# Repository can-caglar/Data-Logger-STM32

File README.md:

# Serial Snooper

The Serial Snooper is a UART data logger with automatic baud rate detection, real-time data stamping and a command-line-interface for configuration, running on an STM32F3 microcontroller.

It is utilised in an R&D setting to easily capture logs from devices to speed up catching software and hardware bugs.

<i> This project started out as a submission for the final project in the course "Making Embedded Systems" by Elecia White, and evolved into a complete functional product used professionally. The report for the project submitted to the course can be found [here](https://docs.google.com/document/d/1QN5CVr99LwbAlFGOjgETou2btL8RMqJVu_yTGeXLMHs/edit?usp=sharing). </i>

## The Final Product

<center>
<image src="resource\hw_image_1.jpg">
<i>PCBA Front</i>
<br>
<br>
<image src="resource\hw_image_2.jpg">
<i>PCBA Back</i>
<br>
<br>
</center>

## Description of Operation

1. Plug in USB (5V - resettable fuse limits current to 500mA incase of short circuits damaging the power source).
2. Device powers up, indicated by the green LED.
3. A short moment later, the red LED lights up, indicating that the SD card was successfully initialised.
4. Plug in DB9 cable for the device you wish to snoop. The baud rate will be automatically detected.
5. The yellow LED will toggle for every character received.
6. The blue LED will toggle for every successful SD card write.
7. When ready, power down the device by removing the USB cable and remove the SD card.

## Schematic

<center>
<image src="HardwareDesign\hardwareImages_v1\schematic_png.PNG">
<i>Partial schematic. At the heart of the device is a STM32F303 microcontroller.</i>
</center>
<br>

The full hardware schematic can be found on [Github](HardwareDesign/hardwareImages_v1/serial_snooper_schematic.pdf).

## Design Block Diagram

<center>

<i>Software Block Diagram</i>
</center>

## Prototype

A prototype board was created to aid development.

Headers have been soldered to a perforated board. A mixture of wire wrapping and soldering used for the connections.

### The working prototype

### Pinouts

# Demo 

All demonstrations below are from the prototype device using the software in this repository.

## Command Line Interface (CLI)

The CLI is used to:

- Ascertain the software version number
- Send commands:
  - Get DIP switch setting.
  - Get the current time.
  - Set the current time.

For example:
<center>

</center>

## Example Data Saved on SD Card

The received data is timestamped and saved to the SD card. The filesystem being used is Fatfs (middleware software for this was provided by STM32 Cube).

In the example below, nearly 30,000 characters were sent over the course of 68 seconds (at 115200 BR) and all data was transferred successfully.

*(The text file below is generated by the Serial Snooper and can be found as resource/example_log.TXT)*

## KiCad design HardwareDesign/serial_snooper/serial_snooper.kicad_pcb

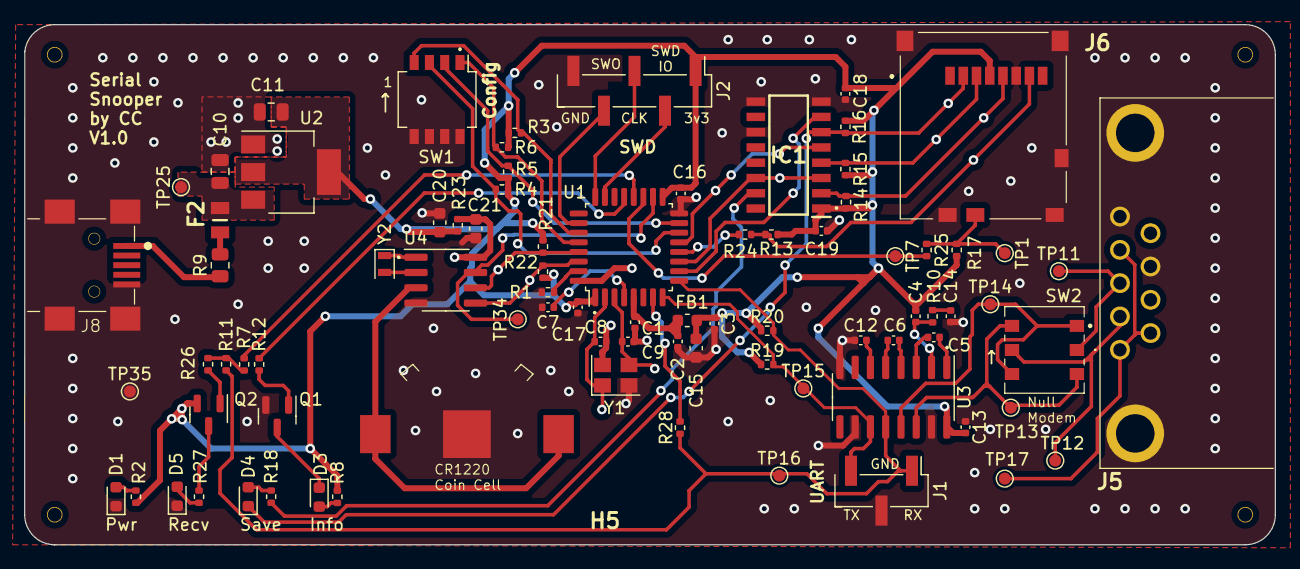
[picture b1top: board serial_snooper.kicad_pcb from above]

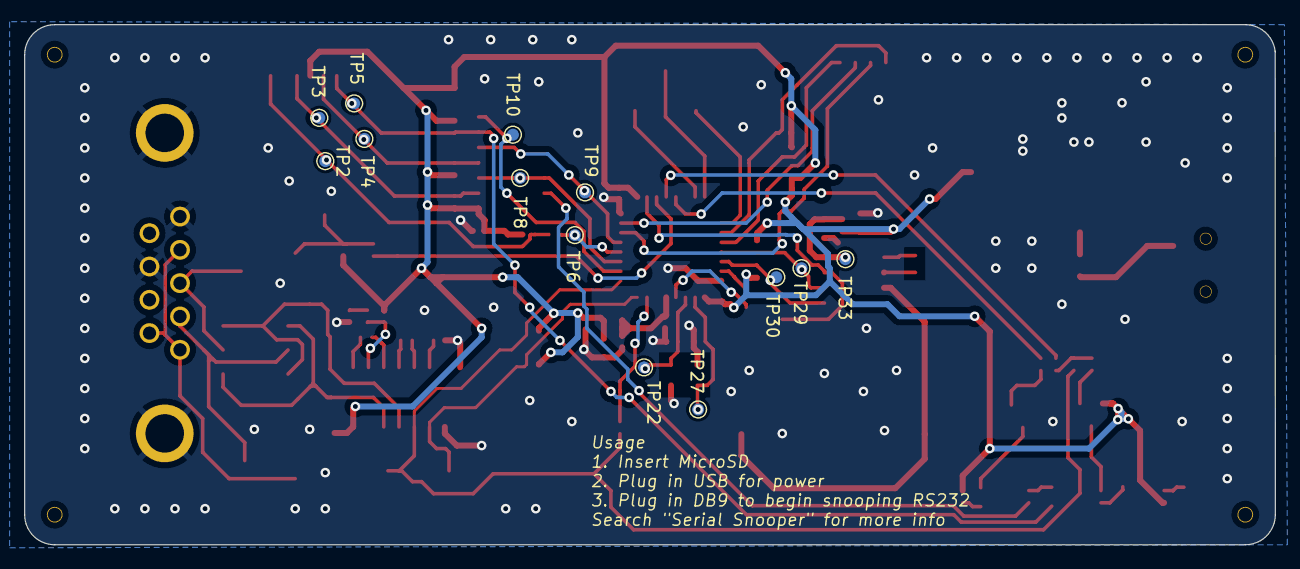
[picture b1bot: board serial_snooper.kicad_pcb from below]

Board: 2 copper layers, 104.0 x 43.2 mm, 101 parts (13 on the bottom side), 61 nets.

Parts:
C1: 10n; C_0402_1005Metric
C2, C3: 1u; C_0402_1005Metric
C4, C5, C6, C7, C12, C13, C14, C16, C17, C18, C19: 100n; C_0402_1005Metric
C8, C9: 15p; C_0402_1005Metric
C10, C11: 22u; C_0805_2012Metric
C15, C20, C21: 10u; C_0603_1608Metric
D1: GREEN; LED_0603_1608Metric
D3: RED; LED_0603_1608Metric
D4: RED_SD; LED_0603_1608Metric
D5: YELLOW; LED_0603_1608Metric
F2: 0ZCK0020FF2G; FUSC2214X100N
FB1: 120R; L_0603_1608Metric
H1, H2, H3, H4: MountingHole; ToolingHole
H5: 2894
IC1: 74HC4050D,653; SOIC127P600X175-16N
J1: Conn_01x03_Pin; PinHeader_1x03_P2.54mm_Vertical_SMD_Pin1Left
J2: Conn_01x05_Pin; PinHeader_1x05_P2.54mm_Vertical_SMD_Pin1Left
J5: L717SDE09P1ACH
J6: Micro_SD_Card_Det1; 5025700893
J8: USB_B_Mini; USB-MINI-10033526-N3212LF
Q1: MMBT3904; SOT-23
Q2: MMBT3906; SOT-23
R1, R3, R4, R5, R6: 10k; R_0402_1005Metric
R2, R12, R18, R23, R26: 1k5; R_0402_1005Metric
R7, R10: DNP; R_0402_1005Metric
R8, R27: 330R; R_0402_1005Metric
R9: 0R; R_0805_2012Metric
R11, R24, R25, R28: 0R; R_0402_1005Metric
R13, R14, R15, R16, R17, R19, R20: 47k; R_0402_1005Metric
R21, R22: 10K; R_0402_1005Metric
SW1: SW_DIP_x04; SW_DIP_SPSTx04_Slide_Omron_A6H-4101_W6.15mm_P1.27mm
SW2: SW_DPDT_x2; DPDT-SMD-MS-22D28G2-B
TP1, TP2, TP3, TP4, TP5, TP6, TP7, TP8, TP9, TP10, TP11, TP12, TP13, TP14, TP15, TP16, TP17, TP22, TP25, TP27, TP29, TP30, TP33, TP34, TP35: TestPoint; TestPoint_Pad_D1.0mm
U1: STM32F303K8T6; LQFP-32_7x7mm_P0.8mm
U2: AMS1117-3.3; SOT-223-3_TabPin2
U3: MAX3232; SOIC-16_3.9x9.9mm_P1.27mm
U4: PCF8523T; SOIC-8_3.9x4.9mm_P1.27mm
Y1: 16MHz; Crystal_SMD_3225-4Pin_3.2x2.5mm
Y2: 32.768; Crystal_SMD_2012-2Pin_2.0x1.2mm

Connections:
+3.3V: C3.1, C4.2, C11.1, C13.2, C15.1, C16.1, C17.1, C18.1, C19.1, C20.1, FB1.1, IC1.1 (VCC), J2.1, J6.4 (VDD), Q2.2 (E), R2.1, R3.1, R4.1, R5.1, R6.1, R8.2, R13.1, R14.1, R15.1, R16.1, R17.1, R19.1, R20.1, R21.1, R22.1, R23.2, U1.1 (VDD), U1.17 (VDD), U2.2 (VO), U3.16 (VCC)
+3.3VA: C1.1, C2.1, FB1.2, U1.5 (VDDA)
/BOOT0: R1.2, U1.31 (BOOT0)
/CARD_DETECT: R25.1, TP7.1, U1.19 (PA9)
/COMMS_LED: R7.1, U1.20 (PA10)
/DIPSWITCH_1: R6.2, SW1.1, U1.28 (PB5)
/DIPSWITCH_2: R5.2, SW1.2, U1.15 (PB1)
/DIPSWITCH_3: R4.2, SW1.3, U1.14 (PB0)
/DIPSWITCH_4: R3.2, SW1.4, U1.27 (PB4)
/HSE_IN: C8.1, TP27.1, U1.2 (PF0), Y1.1
/HSE_OUT: C9.1, TP22.1, U1.3 (PF1), Y1.3
/I2C1_SCL: R21.2, TP29.1, U1.29 (PB6), U4.6 (SCL)
/I2C1_SDA: R22.2, TP30.1, U1.30 (PB7), U4.5 (SDA)
/NRST: C7.1, U1.4 (NRST)
/PWR_LED_C: D1.2 (A), R2.2
/RS232-UART/C1+: C5.1, U3.1 (C1+)
/RS232-UART/C1-: C5.2, U3.3 (C1-)
/RS232-UART/C2+: C6.1, U3.4 (C2+)
/RS232-UART/C2-: C6.2, U3.5 (C2-)
/RS232-UART/DB9_RXD: J5.2, SW2.5 (B), TP12.1
/RS232-UART/DB9_TXD: J5.3, SW2.2 (B), TP11.1
/RS232-UART/R1IN: SW2.1 (A), SW2.6 (C), TP14.1, U3.13 (R1IN)
/RS232-UART/T1OUT: SW2.3 (C), SW2.4 (A), TP13.1, U3.14 (T1OUT)
/RS232-UART/VS+: C4.1, R10.1, U3.2 (VS+)
/RS232-UART/VS-: C12.2, U3.6 (VS-)
/RTC_IRQ: TP34.1, U1.18 (PA8), U4.7 (~INT1/CLKOUT)
/RealtimeClock/Battery+: H5.1 (+), H5.2 (-), U4.3 (VBAT)
/RealtimeClock/RTC_Vdd: C21.1, R23.1, TP33.1, U4.8 (VDD)
/SD-card-adapter/SD_CLK: IC1.2 (1Y), J6.5 (CLK), R14.2, TP3.1
/SD-card-adapter/SD_CS: D4.1 (K), IC1.6 (3Y), J6.2 (DAT3/CD), R16.2, TP5.1
/SD-card-adapter/SD_DETECT: J6.9 (DET), R17.2, R25.2, TP1.1
/SD-card-adapter/SD_DI: IC1.4 (2Y), J6.3 (CMD), R15.2, TP4.1
/SD-card-adapter/SD_DO: J6.7 (DAT0), R13.2, R24.2, TP2.1
/SD-card-adapter/SD_LED_ANODE: D4.2 (A), R18.2
/SPI1_CLK: IC1.3 (1A), IC1.14 (6A), TP8.1, U1.11 (PA5)
/SPI1_CS: IC1.7 (3A), TP10.1, U1.10 (PA4)
/SPI1_MISO: R24.1, TP6.1, U1.12 (PA6)
/SPI1_MOSI: IC1.5 (2A), TP9.1, U1.13 (PA7)
/STATUS_LED: R12.2, U1.21 (PA11)
/SWCLK: J2.3, U1.24 (PA14)
/SWDIO: J2.2, U1.23 (PA13)
/TIM2_CH2: R28.2, U1.7 (PA1)
/TRACE_SWO: J2.4, U1.26 (PB3)
/USART2_RX: J1.1, R11.1, R20.2, R28.1, TP16.1, U1.9 (PA3), U3.12 (R1OUT)
/USART2_TX: J1.3, R19.2, TP15.1, U1.8 (PA2), U3.11 (T1IN)
/VBUS_after_fuse: C10.1, F2.2, TP25.1, U2.3 (VI)
GND: C1.2, C2.2, C3.2, C7.2, C8.2, C9.2, C10.2, C11.2, C12.1, C13.1, C14.2, C15.2, C16.2, C17.2, C18.2, C19.2, C20.2, C21.2, D1.1 (K), D5.1 (K), H5.MP1, IC1.8 (GND), IC1.9 (4A), IC1.11 (5A), J1.2, J2.5, J5.5, J5.8, J5.MH1, J5.MH2, J6.6 (VSS), J6.10 (SHIELD), J8.5 (GND), J8.6 (Shield), Q1.2 (E), R1.1, SW1.5, SW1.6, SW1.7, SW1.8, TP35.1, U1.16 (VSS), U1.32 (VSS), U2.1 (GND), U3.8 (R2IN), U3.10 (T2IN), U3.15 (GND), U4.4 (VSS), Y1.2, Y1.4
unnamed: C14.1, R10.2
unnamed: D3.2 (A), R8.1
unnamed: D3.1 (K), Q1.3 (C)
unnamed: D5.2 (A), R27.1
unnamed: F2.1, R9.2
unnamed: IC1.15 (6Y), R18.1
unnamed: J5.1, J5.4, J5.6, TP17.1
unnamed: J8.1 (VBUS), R9.1
unnamed: Q1.1 (B), R12.1
unnamed: Q2.1 (B), R26.1
unnamed: Q2.3 (C), R27.2
unnamed: R7.2, R11.2, R26.2
unnamed: U4.1 (OSCI), Y2.1
unnamed: U4.2 (OSCO), Y2.2

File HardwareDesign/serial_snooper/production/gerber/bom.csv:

Designator,Footprint,Quantity,Value,LCSC Part #
C1,0402,1,10n,
"C10, C11",0805,2,22u,
"C12, C13, C14, C16, C17, C18, C19, C4, C5, C6, C7",0402,11,100n,
"C15, C20, C21",0603,3,10u,
"C2, C3",0402,2,1u,
"C8, C9",0402,2,15p,
D1,0603,1,GREEN,
D3,0603,1,RED,
D4,0603,1,RED_SD,
D5,0603,1,YELLOW,
F2,FUSC2214X100N,1,0ZCK0020FF2G,
FB1,0603,1,120R,
"H1, H2, H3, H4",ToolingHole,4,MountingHole,
H5,2894,1,2894,
IC1,SOIC127P600X175-16N,1,"74HC4050D,653",C43181
J1,PinHeader_1x03_P2.54mm_Vertical_SMD_Pin1Left,1,Conn_01x03_Pin,C5160786
J2,PinHeader_1x05_P2.54mm_Vertical_SMD_Pin1Left,1,Conn_01x05_Pin,
J5,L717SDE09P1ACH,1,L717SDE09P1ACH,
J6,5025700893,1,Micro_SD_Card_Det1,C429846
J8,USB-MINI-10033526-N3212LF,1,USB_B_Mini,C428494
Q1,SOT-23,1,MMBT3904,
Q2,SOT-23,1,MMBT3906,
"R1, R21, R22, R3, R4, R5, R6",0402,7,10k,
"R10, R7",0402,2,DNP,
"R11, R24, R25, R28",0402,4,0R,
"R12, R18, R2, R23, R26",0402,5,1k5,
"R13, R14, R15, R16, R17, R19, R20",0402,7,47k,
"R27, R8",0402,2,330R,
R9,0805,1,0R,
SW1,SW_DIP_SPSTx04_Slide_Omron_A6H-4101_W6.15mm_P1.27mm,1,SW_DIP_x04,
SW2,DPDT-SMD-MS-22D28G2-B,1,SW_DPDT_x2,C2939266
"TP1, TP10, TP11, TP12, TP13, TP14, TP15, TP16, TP17, TP2, TP22, TP25, TP27, TP29, TP3, TP30, TP33, TP34, TP35, TP4, TP5, TP6, TP7, TP8, TP9",TestPoint_Pad_D1.0mm,25,TestPoint,
U1,LQFP-32_7x7mm_P0.8mm,1,STM32F303K8T6,C118318
U2,SOT-223-3_TabPin2,1,AMS1117-3.3,C351784
U3,SOIC-16_3.9x9.9mm_P1.27mm,1,MAX3232,C193666
U4,SOIC-8_3.9x4.9mm_P1.27mm,1,PCF8523T,C2651516
Y1,Crystal_SMD_3225-4Pin_3.2x2.5mm,1,16MHz,C279610
Y2,Crystal_SMD_2012-2Pin_2.0x1.2mm,1,32.768,C252397

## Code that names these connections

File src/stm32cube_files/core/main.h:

/* USER CODE BEGIN Header */
/**
  ******************************************************************************
  * @file           : main.h
  * @brief          : Header for main.c file.
  *                   This file contains the common defines of the application.
  ******************************************************************************
  * @attention
  *
  * Copyright (c) 2022 STMicroelectronics.
  * All rights reserved.
  *
  * This software is licensed under terms that can be found in the LICENSE file
  * in the root directory of this software component.
  * If no LICENSE file comes with this software, it is provided AS-IS.
  *
  ******************************************************************************
  */
/* USER CODE END Header */

/* Define to prevent recursive inclusion -------------------------------------*/
#ifndef __MAIN_H
#define __MAIN_H

#ifdef __cplusplus
extern "C" {
#endif

/* Includes ------------------------------------------------------------------*/
#include "stm32f3xx_hal.h"

/* Private includes ----------------------------------------------------------*/
/* USER CODE BEGIN Includes */

/* USER CODE END Includes */

/* Exported types ------------------------------------------------------------*/
/* USER CODE BEGIN ET */

/* USER CODE END ET */

/* Exported constants --------------------------------------------------------*/
/* USER CODE BEGIN EC */

/* USER CODE END EC */

/* Exported macro ------------------------------------------------------------*/
/* USER CODE BEGIN EM */

/* USER CODE END EM */

/* Exported functions prototypes ---------------------------------------------*/
void Error_Handler(void);

/* USER CODE BEGIN EFP */
#define CMX_FATFS       (1U << 0)
#define CMX_UART        (1U << 1) // with interrupt
#define CMX_I2C         (1U << 2)
#define CMX_UART_POLL   (1U << 3)

void SystemClock_Config(void);
void CubeMX_SystemInit(unsigned int sys);

/* USER CODE END EFP */

/* Private defines -----------------------------------------------------------*/
// TODO remove the unused peripheral defines
#define CS_I2C_SPI_Pin GPIO_PIN_3
#define CS_I2C_SPI_GPIO_Port GPIOE
#define PC14_OSC32_IN_Pin GPIO_PIN_14
#define PC14_OSC32_IN_GPIO_Port GPIOC
#define PC15_OSC32_OUT_Pin GPIO_PIN_15
#define PC15_OSC32_OUT_GPIO_Port GPIOC
#define PH0_OSC_IN_Pin GPIO_PIN_0
#define PH0_OSC_IN_GPIO_Port GPIOH
#define PH1_OSC_OUT_Pin GPIO_PIN_1
#define PH1_OSC_OUT_GPIO_Port GPIOH
#define OTG_FS_PowerSwitchOn_Pin GPIO_PIN_0
#define OTG_FS_PowerSwitchOn_GPIO_Port GPIOC
#define PDM_OUT_Pin GPIO_PIN_3
#define PDM_OUT_GPIO_Port GPIOC
#define B1_Pin GPIO_PIN_0
#define B1_GPIO_Port GPIOA
#define I2S3_WS_Pin GPIO_PIN_4
#define I2S3_WS_GPIO_Port GPIOA

#define SPI1_SCK_Pin GPIO_PIN_5
#define SPI1_SCK_GPIO_Port GPIOA
#define SPI1_MISO_Pin GPIO_PIN_6
#define SPI1_MISO_GPIO_Port GPIOA
#define SPI1_MOSI_Pin GPIO_PIN_7
#define SPI1_MOSI_GPIO_Port GPIOA

/* USER CODE BEGIN Private defines */
#define SD_CS_Pin GPIO_PIN_4
#define SD_CS_GPIO_Port GPIOA
#define SD_SPI_HANDLE hspi1
/* USER CODE END Private defines */

#ifdef __cplusplus
}
#endif

#endif /* __MAIN_H */

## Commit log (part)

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2022-07-02 feat: function isConfiguredAsOutput - not tested yet
2022-07-02 feat: isConfiguredAsOutput passes tests but needs refactoring
2022-07-13 compiles on target. making it actually work on target too.
    Started to enable peripheral clocks.
    Aded a new GPIOA define such that our RAM version and register version will work
    seamlessly. Will repeat that for GPIOB.
2022-07-17 chore: add gitignore
2022-07-17 refactor: pins and masks now have distinct enums dedicated for them + add more to gitignore
2022-07-17 chore: change name of custom stm2f4 common file to make it easier to understand
2022-07-18 feat: add more steps to init. compiles and passes on target.
2022-07-31 fix: bug in CONF_BITS macro
2022-07-31 refactor: alt function init in its own function
2022-07-31 refactor: GPIO pin mask is now a typedef uint16. Passes on STM32.
    This is due to the disparity between the dev PC and STM32 compilers. The STM32 compiler enums happened to be 16 bits, dev PC 32 bits. now the
    type size is equal on both devices. The test that used to check this has been removed and another added, see diff.
    No longer checking size of mask as it is now protected by the size of
    uint16.
2022-08-21 feat: uart read/write 1 byte. start CLI tests
2022-08-21 test: start State Machine with mocks of receiver
2022-08-21 test: begin testing receiver. add custom type to cmock
2022-08-21 test: add buffer filling tests to MyReceiver
2022-08-27 test: CLI, add quick test for help
2022-08-27 test: testing the input with bad input. increase size of cmd to 20
2022-08-28 refactor: MyProcessor code. Add it to Keil.
2022-09-04 test: MyReceiver now uses new Terminal module and doesnt access uart directly
2022-09-04 test: add main. change \n to \r. add TODOS for UART
2022-09-16 refactor state machine- just two states remaining
2022-09-27 refactor: update names to be more meaningful, add comments
2022-10-02 update todo
2022-10-02 add stm32 HAL fake headers, ceedling compiles
2022-10-02 led module init uses fake HAL directly - passes all tests
2022-10-02 refactor: fake headers
2022-10-02 refactor: use HAL NVIC directly for button. update yaml file- but doesn't seem to make difference
2022-10-02 refactor: remove unused hal adapter files
2022-10-02 docs: update todo
2022-10-03 refactor: remove system hal adapter and use the hal directly for all modules
2022-10-03 chore: update Keil dependencies; compiles on Keil
2022-10-16 feat: port Fatfs to this project
2022-10-22 feat: add SD card module init, close and write functions
2022-10-23 feat: CLI can write to SD card
2022-10-29 migrate: replace fatfs core files for stm32f0, replace cubeMX generated code
2022-10-29 migrate: update tests. all passes now
    required some changes to the yml file and updates to some references to
    defined used in stm32 libraries.
2022-10-30 migrate: update test fakes and the new gpios for this board. fix warnings
2022-10-30 refactor: remove 'hardware' TDD tests as no longer using them and tidy RCC module
2022-10-30 feat: add dip switch module
2022-10-30 fix: fix writeSD cmd when no params passed. update help tests
2022-10-30 feat: add app decider module
2022-10-30 feat: decide between applications at boot
2022-11-06 feat: add UART from CubeMX
2022-11-06 refactor: cubemx generated init function rename
2022-11-06 test: get hal_uart mock compiling
2022-11-07 feat: add serial snooper high level logic
2022-11-07 feat: add circular buffer module
2022-11-07 feat: add circ buf to CLI
2022-11-07 chore: add new files to Keil
2022-11-08 feat: snooping app uart on interrupt, saves to circular buffer
2022-11-09 feat: add i2c driver from cubemx
2022-11-10 fix: RTC seconds now correct. add getTime to CLI. low level init now the responsibility of modules (except fatfs for now)
2022-11-10 optimise: remove unused "say" command to save space
2022-11-11 feat: add write time ability to RTC module
2022-11-11 feat: set time by stopping and restarting osc
2022-11-11 fix: warnings on RTC module
2022-11-11 optimise: reduce fatfs size via configs
2022-11-11 optimise: CLI to use HAL UART (deleted my CMSIS one) to save space
2022-11-11 feat: toggle LED in HAL error handler. max BR is no longer 960k as init fails
2022-11-14 fix: uart and i2c pulled up to prevent bad data to peripherals and circ buffer no longer overwrites. instead it will not fill it in
2022-11-14 refactor: increase circ buf size to 512: use fatfs tiny, remove readdip command
2022-11-14 feat: increase circ buf size to 1024
2022-11-14 refactor: optimise time stamp use lookup instead of printf and reduce size of timestamp itself
2022-11-19 feat: set time via CLI
2022-11-19 feat: expand timestamps
    was "m hh:mm:ss> "
    now "[yy-mm-dd hh:mm:ss] "
2022-11-19 optimise: remove calls to MyGPIO module as its no longer needed. Remove controller module.
2022-11-19 chore: move files out of folders
2022-11-19 chore: update file structure
    - move files to their own folders and update Keil dirs
2022-11-19 docs: update readme with more prototype board details
2022-11-20 feat: spi speed for sd card increased to 18 MHz (from less than 1 MHz)
2022-11-20 fix: timestring will return 0s if time buffer is corrupt
2022-11-21 fix: link to final report on readme + update prototype img
2023-01-08 docs: Update README as no more data losses
    Increasing SPI clock speed to maximum meant no data is lost currently. Had to update README which was still mentioning data losses.
2023-01-21 feat: indicate via LED when data is lost
    Red LED on pin A11 will light up if data is lost. it remains on until uC
    is reset.
2023-01-28 feat: add circ buf get size to module
2023-01-28 feat: MySD module can return opened file size
2023-01-28 refactor: move system inits outside of serial snooper module
    it doesnt make sense they are in this layer
2023-01-28 refactor: move across tests for the operation of write/flush sd
    they go in their own module and own functions.
    this is one of the steps of separating the
    operations in the SerialSnooper_Run into their own module
    and individual functions.
    the tests were made very complicated simply because of
    the fact that the Run() function was doing too many things at once.
2023-01-29 (to squash) just saving as system is working currently but tests won't pass as I'm rewriting serial snooper
2023-01-29 feat: scheduler periodically calls more than 1 function
2023-01-29 feat: cap the max amount of tasks
2023-01-29 docs: add comments
2023-01-29 refactor: (in progress) no longer access struct ptr for checking if new data present
    The pointer is supposed to be opaque. this commit is an interim one.
    full refactor not yet done
2023-01-29 refactor: (in progress) remove calls to concrete struct
2023-01-29 refactor: (in progress) remove dependence on circ buf module
2023-01-29 refactor: use actual function for grabbing data context rather than fn ptr
    We don't need the added flexibility
2023-01-29 feat: add DataHolder module (very heavily mocked, may need refactoring)
2023-01-29 feat: OpenLogFile operation update
    Will open new file if none exists,
    or if above max file size
    or if above a lower threshold file size but system is "idle"
2023-01-29 feat: data holder returns file size
2023-02-04 refactor: DataHolder no longer uses a context
    it didn't need it. plus it's more efficient to "lazily" get data needed than do it
    all in one go
2023-02-04 chore: comments + improve var names
2023-02-04 chore: rename SerialSnooper module to MyScheduler
    The name was confusing.
2023-02-04 test: add fake SD card module
2023-02-04 test: make it more obvious when module not initted
    Filename returned will suggest it wasn't initted for the fake time
    string module
    Fake data can be injected without module being reset
2023-02-04 test: fake SD card size updates as we add data instead of being set
    This means it will update live, closer emulating a real sd card
2023-02-05 feat: limit file size and open new one when a max size is reached
2023-02-12 migrate to stm32f303k8 from stm32f031k6
    compiles but not tested on target.
    - updated files
    - change i2c1 pins from pa9,10 to pb6,7
    - change usart from usart1 to usart2 and update alt function value
    - update spi1 alt func value
    - remove PREDIV assignment in RCC typedef as new driver doesnt have it
2023-02-20 fix: increase processor and SPI speed, remove i2c
    - APB2 bus at 72 MHz
    - SPI at 36 MHz
    - I2C pins were conflicting with SPI pins due to a solder bridge on the
    F3 nucleo. Removed them temporarily. The plan is to use internal RTC
    anyway so there won't be a need for I2C line.
2023-02-21 feat: circular buf size increased from 8192 to 10300
    circular buffer no longer has to be power of 2. the speed difference
    appears to be negligible.
    reduced stack and heap size to accomodate increase of circ buffer size
2023-02-21 test: update SystemOperations tests to use fake modules
    test: fix bug in fakeSD module where file size was updating before
    flushing. also add ability to change what error message is returned.
2023-02-23 docs: add profiling spreadsheet
2023-02-23 testing speed of filling up circular buffer with Teraterm
2023-02-23 reduce stack usage w/compiler switches. test main program loop, record last 32 readings > 50 ms
2023-02-24 profiling lower level fatfs
2023-02-25 fix: significantly improve block write speed, update version num to 2
    - logic analyser inspection showed that for every byte transferred,
    which takes 1us, there was a 14 us delay. The low user_diskio_spi.c
    driver was sending bytes 1 at a time via the HAL API. Updated it to
    send multi bytes. Transfer rate has more than doubled.
    - update version number to 2
2023-02-25 fix: re-enable I2C now that the wiring is done
    + tidy comments
2023-03-07 feat: add file name iterator module
    docs: update todo
    refactor: update variable names in system operations module
2023-03-08 refactor: init name iterator module in system operations. all tests passing
2023-03-18 test: reads from file on sd to determine first file name. doesnt yet write to this file though. all tests passing as they are
2023-03-19 test: open/close multiple files
2023-03-19 test: rename functions which makes the module make a lot more sense
    file is open -> file exists
    file close -> file delete
    file open -> file create
    These changes made a lot more sense with what the functions were doing.
    Few more tests have been added which was made a lot easier with the new
    responsibilities of these functions.
2023-03-19 docs: update todo list
2023-03-25 test: code coverage + experimental fake filesystem code
2023-03-25 test: begin fatfs tests
2023-03-29 test: refactor tests
    also fix yaml file file separators
2023-04-01 feat: respect open modes, increase buffer size
    started implementing "create always" mode.
    testing writing to multiple files open at same time
    testing writing long message (1000 chars)
2023-04-01 feat: (fake fatfs) implement all different open mode behaviour
    feat: fake file system has a seek function
2023-04-07 test: start using new fatfs fake module in other tests
2023-04-08 test: fakeff file open fails if file was already open
    test: add f_close to fakeff file
    test: fakeff f_sync and f_close will fail if file not open
    test: fakeff f_close will flush contents of file buffer
    test: MySD tests for LED turning on and opening consecutive files
2023-04-10 test: Finish MySD test rewrite
    It now uses the new fakeff module.
    feat: MySD WriteString is now a macro
    Makes more sense this way - and makes tests less tedious since
    we don't have to test the macro.
2023-04-15 test: SystemOperations_Flush tests added using new fake api
2023-04-16 test: MyApp tests updated.
    Separated MyApp to two: init and infinite loop
    Made READ_FILE macro visible to other tests.
    Add fakefilesystem dump function to print contents.
    Tidied SystemOperations
    + Add some helpers
2023-04-16 feat: remembers last log file opened on powerup
    using stm32 flash to store log file name and retriveving it upon start
    up.
    added boilerplate code for flash access and the fakes for it.
2023-05-14 test: get started with auto baud rate detection
2023-05-16 feat: auto baud rate (sw seemingly ready but hw not working)
    - add new abstractions: MyUART, autobaudrate, MyTimer
    - add fakes for the HW dependent abstractions (MyUART and MyTimer)
    - add tests to ensure autobaudrate works based on an input capture
    - add tests to MyApp to ensure UART is configured with the correct baud
    rate
    all tests passing however HW tests show that the timer isn't
2023-06-24 fix: update code to match PCB
    - remove pullup on DIP switch as we have hardware pullups
    - light up the "info" led when SD card is detected. the "save" led isn't
    lighting, I think the current limiting resistor is too large.
    - remove error_indicator LED. we will use the "info" led for that
    function in the future once the blue LED resistor issue is fixed.
    hardware:
2023-07-29 fix: make 19200 baud + add hex file to release folder
